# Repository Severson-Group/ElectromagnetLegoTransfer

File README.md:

# LEGO STEM Project Modeling and Design 

In-progress repository of all modelling, CAD files and code for a STEM outreach project utilizing LEGOs and electromagnets.

## Getting Started

### Matlab

All modelling was done in Matlab R2018A.

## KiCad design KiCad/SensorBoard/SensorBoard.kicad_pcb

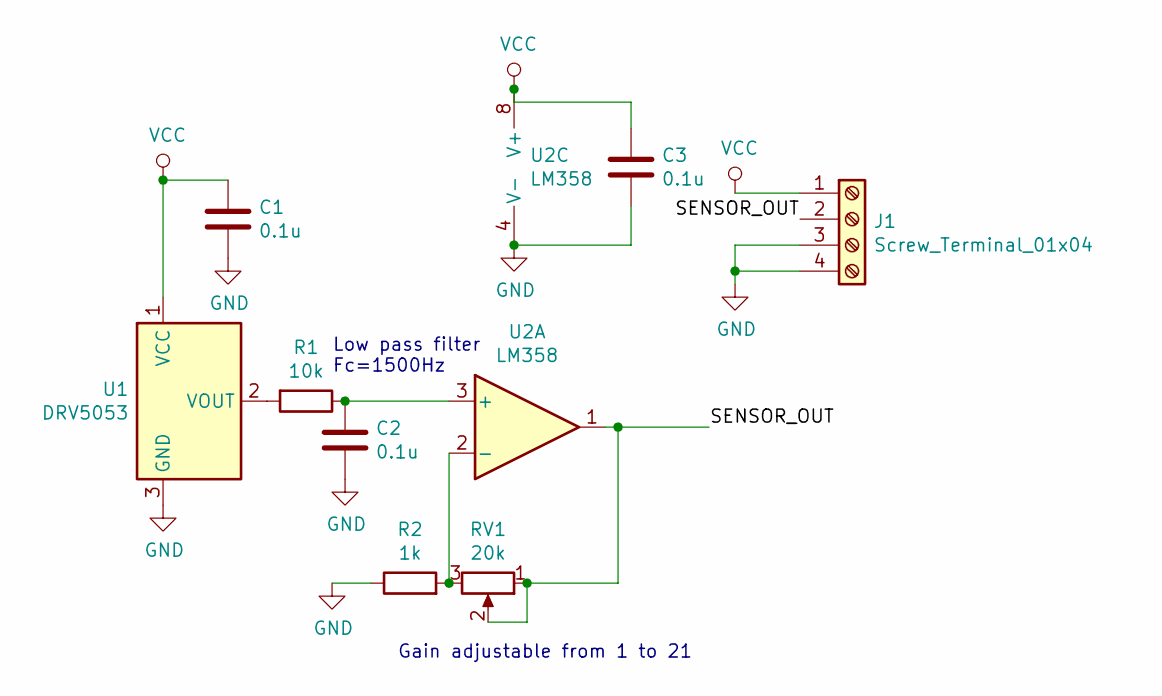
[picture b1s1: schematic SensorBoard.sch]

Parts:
C1, C2, C3: 0.1u; C_Disc_D3.8mm_W2.6mm_P2.50mm
J1: Screw_Terminal_01x04; TerminalBlock_TE_282834-4_1x04_P2.54mm_Horizontal
R1: 10k; R_Axial_DIN0204_L3.6mm_D1.6mm_P7.62mm_Horizontal
R2: 1k; R_Axial_DIN0204_L3.6mm_D1.6mm_P7.62mm_Horizontal
RV1: 20k; Potentiometer_Bourns_3339P_Vertical
U1: DRV5053; HallEffectSensor
U2: LM358; DIP-8_W7.62mm

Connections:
/SENSOR_OUT: J1.2, RV1.1, RV1.2, U2.1
GND: C1.2, C2.2, C3.2, J1.3, J1.4, R2.1, U1.3 (GND), U2.4 (V-)
unnamed: C2.1, R1.1, U2.3 (+)
unnamed: R1.2, U1.2 (VOUT)
unnamed: R2.2, RV1.3, U2.2 (-)
VCC: C1.1, C3.1, J1.1, U1.1 (VCC), U2.8 (V+)

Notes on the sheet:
Low pass filter Fc=1500Hz
Gain adjustable from 1 to 21

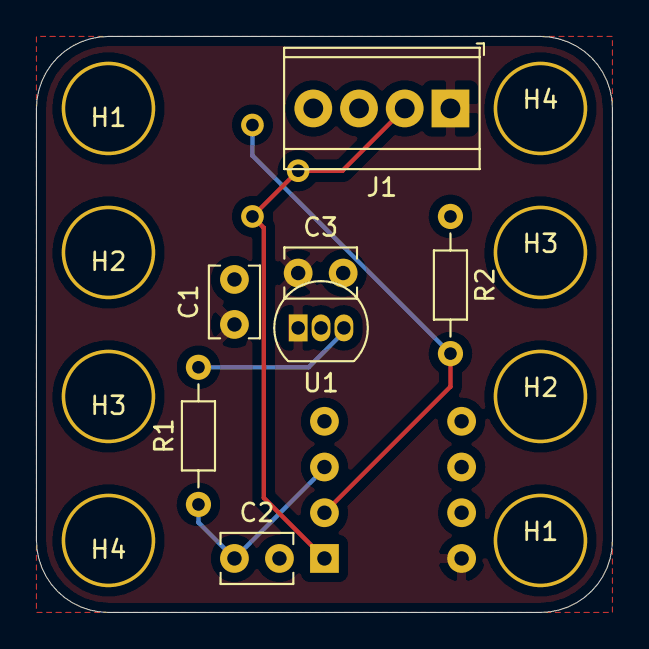
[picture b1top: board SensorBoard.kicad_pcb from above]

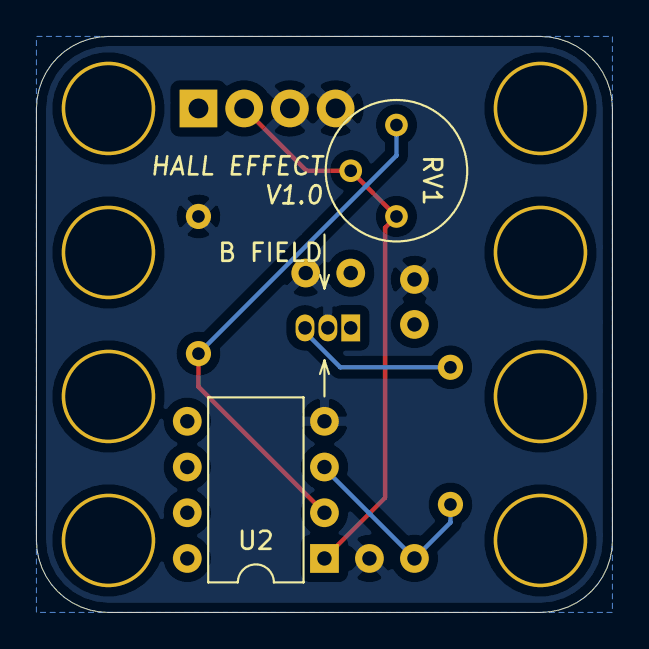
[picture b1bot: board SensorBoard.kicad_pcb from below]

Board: 2 copper layers, 32.0 x 32.0 mm, 17 parts (2 on the bottom side), 6 nets.

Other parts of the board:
H1, H1#2, H2, H2#2, H3, H3#2, H4, H4#2: MountingHole_Pad; LEGO_CONNECTOR_PAD

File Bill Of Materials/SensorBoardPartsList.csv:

Part Name,On Board Designation,Part Number (Digikey),Link,Price,Quantity Req 
DRV5053,U1,296-38604-1-ND,https://www.digikey.com/product-detail/en/texas-instruments/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,$0.98,1
LM358,U2,296-1395-5-ND,https://www.digikey.com/product-detail/en/texas-instruments/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,$0.37,1
20K Trimpot (not required),RV1,3306P-203-ND,https://www.digikey.com/product-detail/en/bourns-inc/3306P-1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,$0.40,1
1K Through-Hole Resistor,R2,N/A,N/A,$0.00,1
10K Through-Hole Resistor,R1,N/A,N/A,$0.00,1
0.1uF Capacitor (Ceramic),"C1,C2,C3",N/A,N/A,$0.00,3
Jumpers (Various Lengths),J1,N/A,N/A,$0.00,1

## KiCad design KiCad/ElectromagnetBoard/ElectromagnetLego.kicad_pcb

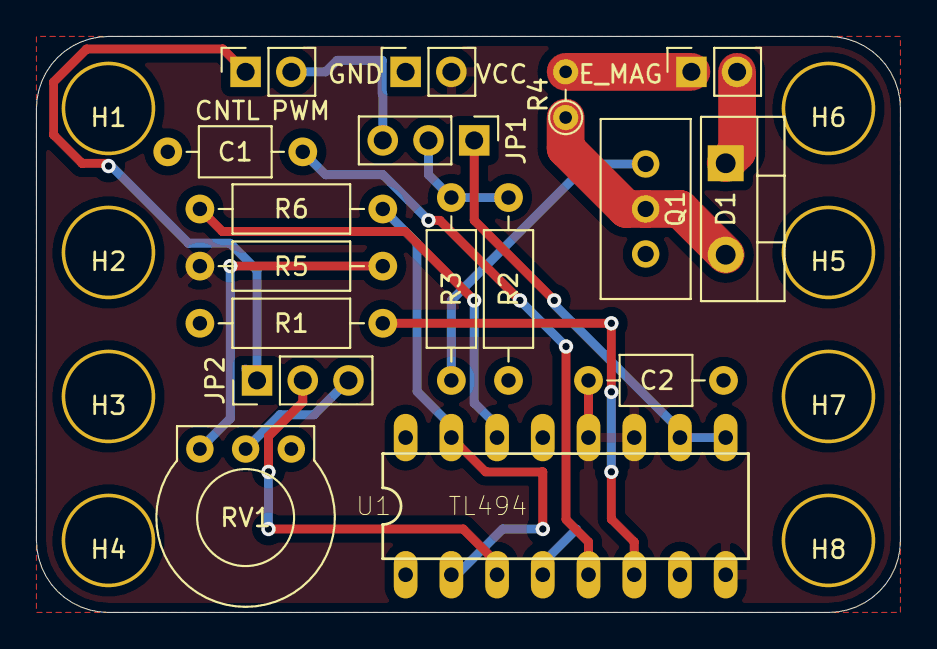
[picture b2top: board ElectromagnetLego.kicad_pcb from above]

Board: 2 copper layers, 48.0 x 32.0 mm, 25 parts (0 on the bottom side), 17 nets.

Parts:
C1, C2: 0.1u; C_Axial_L3.8mm_D2.6mm_P7.50mm_Horizontal
D1: MBR735; TO-220-2_Vertical
EX: Screw_Terminal_01x02; PinSocket_1x02_P2.54mm_Vertical
H1, H2, H3, H4, H5, H6, H7, H8: MountingHole_Pad; LEGO_CONNECTOR_PAD
J2, J3: Screw_Terminal_01x02; PinSocket_1x02_P2.54mm_Vertical
JP1, JP2: Jumper_3_Bridged12; PinHeader_1x03_P2.54mm_Vertical
Q1: IPP052NE7N3
R1, R5: 10K; R_Axial_DIN0207_L6.3mm_D2.5mm_P10.16mm_Horizontal
R2: 1K; R_Axial_DIN0207_L6.3mm_D2.5mm_P10.16mm_Horizontal
R3: 61; R_Axial_DIN0207_L6.3mm_D2.5mm_P10.16mm_Horizontal
R4: 0.1; R_Axial_DIN0204_L3.6mm_D1.6mm_P2.54mm_Vertical
R6: 50K; R_Axial_DIN0207_L6.3mm_D2.5mm_P10.16mm_Horizontal
RV1: 4K RPOT; BOURNS_3352_TRIMPOT
U1: TL494

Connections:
/EMAG_FLYBK: D1.1, J2.2
/EMAG_IN: J2.1, R4.2
/EXTERNAL_CNTL: EX.1, JP2.1
/EXTERNAL_PWM: EX.2, JP1.3
/MANUAL_CNTL: JP2.3, RV1.2
/PWM_IN: JP1.2, R2.1, R3.2
/R_SENSE_L: D1.2, Q1.2, R4.1
GND: C1.2, C2.2, H1.1, H2.1, H3.1, H4.1, H5.1, H6.1, H7.1, H8.1, J3.1, Q1.3, R1.2, R2.2, RV1.3, U1.1, U1.4, U1.7, U1.13, U1.16
unnamed: C1.1, U1.5
unnamed: JP1.1, U1.9, U1.10
unnamed: JP2.2, U1.3
unnamed: Q1.1, R3.1
unnamed: R1.1, U1.6
unnamed: R5.2, RV1.1
unnamed: R6.1, U1.14
unnamed: R6.2, U1.2, U1.15
VCC: C2.1, J3.2, R5.1, U1.8, U1.11, U1.12

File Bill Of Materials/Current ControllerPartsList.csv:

Part Name,On Board Designation,Part Number (Digikey),Link,Price,Quantity Req
TL494,U1,296-10194-5-ND,https://www.digikey.com/product-detail/en/texas-instruments/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,$0.65,1
IPP052NE7N3,Q1,IPP052NE7N3GXKSA1-ND,https://www.digikey.com/product-detail/en/infineon-technolog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,$2.07,1
MBR735,D1,MBR735GOS-ND,https://www.digikey.com/product-detail/en/on-semiconductor/M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,$0.65,1
4K Trimpot (not required),RV1,3352T-502LF-ND,https://www.digikey.com/products/en?mpart=3352T-1-502LF&v=118,$1.85,1
0.1 Through-Hole Resistor (not required),R4,N/A,N/A,$0.00,1
20-60 Through-Hole Resistor,R3,N/A,N/A,$0.00,1
1K Through-Hole Resistor,R2,N/A,N/A,$0.00,1
10K Through-Hole Resistor,"R1,R5",N/A,N/A,$0.00,2
50K Through-Hole Resistor,R6,N/A,N/A,$0.00,1
0.1uF Capacitor (Ceramic),"C1,C2",N/A,N/A,$0.00,2
Jumpers (Various Lengths),"JP1,JP2,J1,J2,J3",N/A,N/A,$0.00,5

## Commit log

2019-10-30 Modelled and linearized electromag system
2019-11-01 Add closed loop control simulation
2019-11-01 add switched mode ltspice model
2019-11-01 Add PWM MFET LTspice simulation
2019-11-01 updade PWM controller input
2019-11-02 add Solidworks STL and models
2019-11-02 add README
2019-11-02 fix unity feedback PD control
2019-11-02 update switched mode controller
2019-11-02 add PID control simulation
2019-11-02 Add closed loop simulink model with PID saturation
2019-11-05 change switched mode controller to use LT6992
2019-11-06 fix system operating point linearization
2019-11-06 add closed loop hall effect sensor model
2019-11-06 update README to include LTSpice instructions
2019-11-06 add KiCad controller schematic
2019-11-06 fix force graph title
2019-11-06 create force solver
2019-11-06 remove LTSpice file references
2019-11-06 fix linearization data name
2019-11-08 create KiCad sensor board
2019-11-08 fix TL494 simulation
2019-11-16 Add snap fit to bolt head
2019-11-16 Add wire holder hole to model
2019-11-16 Fix wire hole size and bolt case
2019-11-16 Add threads to core bottom
2019-11-16 increase core top bolt outer diameter to 20.37mm
2019-11-22 Create arduino PWM testing
2019-11-22 Change thread size to M10-1.5 from M10-1.25
2019-11-22 Increase top and bottom snap post diameter
    Increase top snap post by 0.6mm
    Increase bottom snap post by 0.9mm
2019-11-22 Update sensor amplification sim
2019-11-22 Add KiCad gerber files
2019-12-01 add rib to electromag top
2019-12-01 fix thread offset and expand wire hole
2019-12-18 Add user-defined PID values
2019-12-19 Update PID controller
2020-01-22 Update KiCad
2020-01-22 update sensor board
2020-01-22 update Matlab Simulation
2020-01-22 update LTSpice Simulation
2020-01-26 Fix issues with matlab simulation
2020-01-26 Update switched mode controller sim
2020-01-26 Add BOM for boards and misc
2020-01-26 Fix current controller BOM name
2020-01-26 Add comments to control code
2020-01-27 Add electromagnet wire to BOM
